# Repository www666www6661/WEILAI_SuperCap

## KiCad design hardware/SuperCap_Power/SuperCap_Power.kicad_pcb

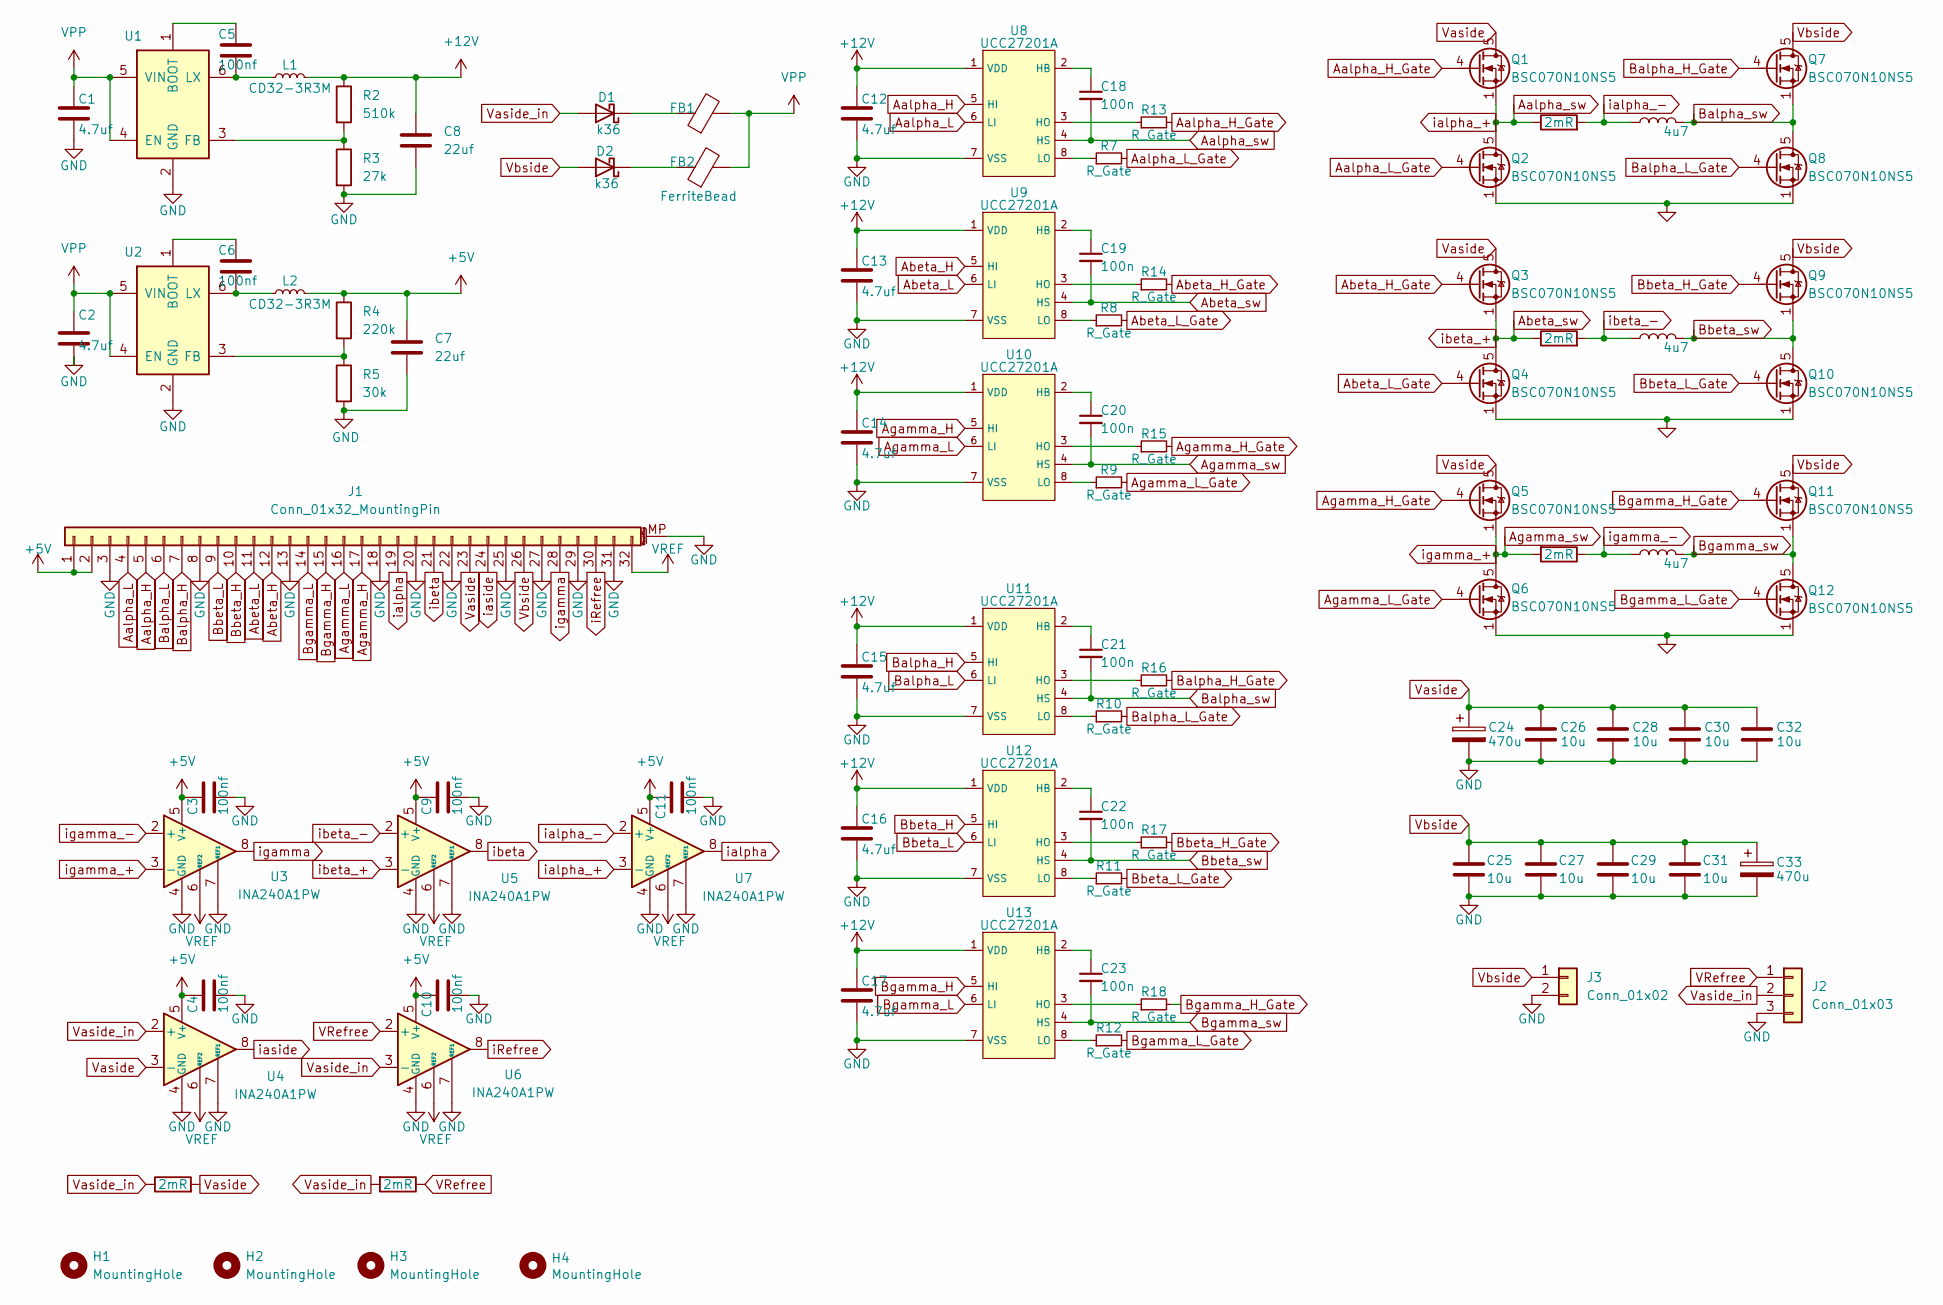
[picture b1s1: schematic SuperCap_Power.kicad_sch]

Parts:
C1, C2: 4.7uf; C_0805_2012Metric
C3, C4, C5, C6, C9, C10, C11: 100nf; C_0603_1608Metric_Pad1.08x0.95mm_HandSolder
C7, C8: 22uf; C_0603_1608Metric_Pad1.08x0.95mm_HandSolder
C12, C13, C14, C15, C16, C17: 4.7uf; C_0603_1608Metric_Pad1.08x0.95mm_HandSolder
C18, C19, C20, C21, C22, C23: 100n; C_0603_1608Metric
C24, C33: 470u; C_Radial_D10.0mm_H20.0mm_P5.00mm
C25, C26, C27, C28, C29, C30, C31, C32: 10u; C_1206_3216Metric
D1, D2: k36; D_SOD-123F
FB1, FB2: FerriteBead; L_0603_1608Metric
H1, H2, H3, H4: MountingHole; MountingHole_3.2mm_M3
J1: Conn_01x32_MountingPin; Hirose_FH12-32S-0.5SH_1x32-1MP_P0.50mm_Horizontal
J2: Conn_01x03; 1_03
J3: Conn_01x02; 01_02
L1, L2: CD32-3R3M; tolerance 20 %; MPN CD32-3R3M
L3, L4, L5: 4u7; L_Bourns_SRP1050WA
Q1, Q2, Q3, Q4, Q5, Q6, Q7, Q8, Q9, Q10, Q11, Q12: BSC070N10NS5; TDSON-8-1
R1, R6, R19, R20, R21: 2mR; R_0612_1632Metric
R2: 510k; R_0603_1608Metric_Pad0.98x0.95mm_HandSolder
R3: 27k; R_0603_1608Metric_Pad0.98x0.95mm_HandSolder
R4: 220k; R_0603_1608Metric_Pad0.98x0.95mm_HandSolder
R5: 30k; R_0603_1608Metric_Pad0.98x0.95mm_HandSolder
R7, R8, R9, R10, R11, R12, R13, R14, R15, R16, R17, R18: R_Gate; R_0603_1608Metric
U1, U2: ME3121AM6G; SOT-23-6; MPN ME3121AM6G
U3, U4, U5, U6, U7: INA240A1PW; TSSOP-8_4.4x3mm_P0.65mm
U8, U9, U10, U11, U12, U13: UCC27201A; SOIC-8_3.9x4.9mm_P1.27mm

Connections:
+5V: C3.2, C4.2, C7.2, C9.2, C10.2, C11.2, J1.1, J1.2, L2.2, R4.1, U3.5 (V+), U4.5 (V+), U5.5 (V+), U6.5 (V+), U7.5 (V+)
+12V: C8.2, C12.1, C13.1, C14.1, C15.1, C16.1, C17.1, L1.2, R2.1, U8.1 (VDD), U9.1 (VDD), U10.1 (VDD), U11.1 (VDD), U12.1 (VDD), U13.1 (VDD)
Aalpha_H: J1.5, U8.5 (HI)
Aalpha_H_Gate: Q1.4 (G), R13.2
Aalpha_L: J1.4, U8.6 (LI)
Aalpha_L_Gate: Q2.4 (G), R7.2
Aalpha_sw: C18.2, Q1.1 (S), Q1.2 (S), Q1.3 (S), Q2.5 (D), R19.1, U7.3 (-), U8.4 (HS)
Abeta_H: J1.12, U9.5 (HI)
Abeta_H_Gate: Q3.4 (G), R14.2
Abeta_L: J1.11, U9.6 (LI)
Abeta_L_Gate: Q4.4 (G), R8.2
Abeta_sw: C19.2, Q3.1 (S), Q3.2 (S), Q3.3 (S), Q4.5 (D), R20.1, U5.3 (-), U9.4 (HS)
Agamma_H: J1.17, U10.5 (HI)
Agamma_H_Gate: Q5.4 (G), R15.2
Agamma_L: J1.16, U10.6 (LI)
Agamma_L_Gate: Q6.4 (G), R9.2
Agamma_sw: C20.2, Q5.1 (S), Q5.2 (S), Q5.3 (S), Q6.5 (D), R21.2, U3.3 (-), U10.4 (HS)
Balpha_H: J1.7, U11.5 (HI)
Balpha_H_Gate: Q7.4 (G), R16.2
Balpha_L: J1.6, U11.6 (LI)
Balpha_L_Gate: Q8.4 (G), R10.2
Balpha_sw: C21.2, L3.2, Q7.1 (S), Q7.2 (S), Q7.3 (S), Q8.5 (D), U11.4 (HS)
Bbeta_H: J1.10, U12.5 (HI)
Bbeta_H_Gate: Q9.4 (G), R17.2
Bbeta_L: J1.9, U12.6 (LI)
Bbeta_L_Gate: Q10.4 (G), R11.2
Bbeta_sw: C22.2, L4.2, Q9.1 (S), Q9.2 (S), Q9.3 (S), Q10.5 (D), U12.4 (HS)
Bgamma_H: J1.15, U13.5 (HI)
Bgamma_H_Gate: Q11.4 (G), R18.2
Bgamma_L: J1.14, U13.6 (LI)
Bgamma_L_Gate: Q12.4 (G), R12.2
Bgamma_sw: C23.2, L5.2, Q11.1 (S), Q11.2 (S), Q11.3 (S), Q12.5 (D), U13.4 (HS)
GND: C1.2, C2.2, C3.1, C4.1, C7.1, C8.1, C9.1, C10.1, C11.1, C12.2, C13.2, C14.2, C15.2, C16.2, C17.2, C24.2, C25.1, C26.1, C27.1, C28.1, C29.1, C30.1, C31.1, C32.1, C33.2, J1.3, J1.8, J1.13, J1.18, J1.20, J1.22, J1.25, J1.27, J1.29, J1.31, J1.MP (MountPin), J2.3, J3.2, Q2.1 (S), Q2.2 (S), Q2.3 (S), Q4.1 (S), Q4.2 (S), Q4.3 (S), Q6.1 (S), Q6.2 (S), Q6.3 (S), Q8.1 (S), Q8.2 (S), Q8.3 (S), Q10.1 (S), Q10.2 (S), Q10.3 (S), Q12.1 (S), Q12.2 (S), Q12.3 (S), R3.2, R5.2, U1.2 (GND), U2.2 (GND), U3.1 (GND), U3.4 (GND), U3.7 (REF1), U4.1 (GND), U4.4 (GND), U4.7 (REF1), U5.1 (GND), U5.4 (GND), U5.7 (REF1), U6.1 (GND), U6.4 (GND), U6.7 (REF1), U7.1 (GND), U7.4 (GND), U7.7 (REF1), U8.7 (VSS), U9.7 (VSS), U10.7 (VSS), U11.7 (VSS), U12.7 (VSS), U13.7 (VSS)
unnamed: D1.1 (K), FB1.1
unnamed: D2.1 (K), FB2.1
unnamed: C5.2, U1.1 (BOOT)
unnamed: R2.2, R3.1, U1.3 (FB)
unnamed: C5.1, L1.1, U1.6 (LX)
unnamed: C6.2, U2.1 (BOOT)
unnamed: R4.2, R5.1, U2.3 (FB)
unnamed: C6.1, L2.1, U2.6 (LX)
unnamed: C18.1, U8.2 (HB)
unnamed: R13.1, U8.3 (HO)
unnamed: R7.1, U8.8 (LO)
unnamed: C19.1, U9.2 (HB)
unnamed: R14.1, U9.3 (HO)
unnamed: R8.1, U9.8 (LO)
unnamed: C20.1, U10.2 (HB)
unnamed: R15.1, U10.3 (HO)
unnamed: R9.1, U10.8 (LO)
unnamed: C21.1, U11.2 (HB)
unnamed: R16.1, U11.3 (HO)
unnamed: R10.1, U11.8 (LO)
unnamed: C22.1, U12.2 (HB)
unnamed: R17.1, U12.3 (HO)
unnamed: R11.1, U12.8 (LO)
unnamed: C23.1, U13.2 (HB)
unnamed: R18.1, U13.3 (HO)
unnamed: R12.1, U13.8 (LO)
VPP: C1.1, C2.1, FB1.2, FB2.2, U1.4 (EN), U1.5 (VIN), U2.4 (EN), U2.5 (VIN)
VREF: J1.32, U3.6 (REF2), U4.6 (REF2), U5.6 (REF2), U6.6 (REF2), U7.6 (REF2)
VRefree: J2.1, R6.1, U6.2 (+)
Vaside: C24.1, C26.2, C28.2, C30.2, C32.2, J1.23, Q1.5 (D), Q3.5 (D), Q5.5 (D), R1.2, U4.3 (-)
Vaside_in: D1.2 (A), J2.2, R1.1, R6.2, U4.2 (+), U6.3 (-)
Vbside: C25.2, C27.2, C29.2, C31.2, C33.1, D2.2 (A), J1.26, J3.1, Q7.5 (D), Q9.5 (D), Q11.5 (D)
iRefree: J1.30, U6.8
ialpha: J1.19, U7.8
ialpha_-: L3.1, R19.2, U7.2 (+)
iaside: J1.24, U4.8
ibeta: J1.21, U5.8
ibeta_-: L4.1, R20.2, U5.2 (+)
igamma: J1.28, U3.8
igamma_-: L5.1, R21.1, U3.2 (+)

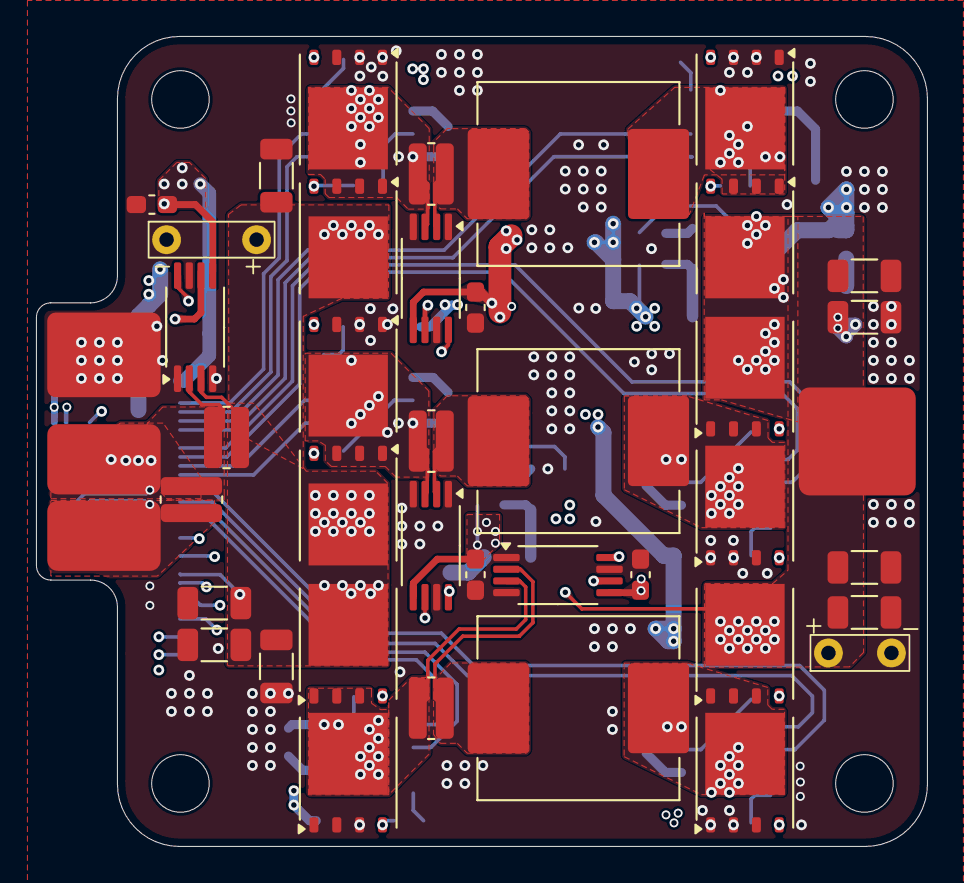
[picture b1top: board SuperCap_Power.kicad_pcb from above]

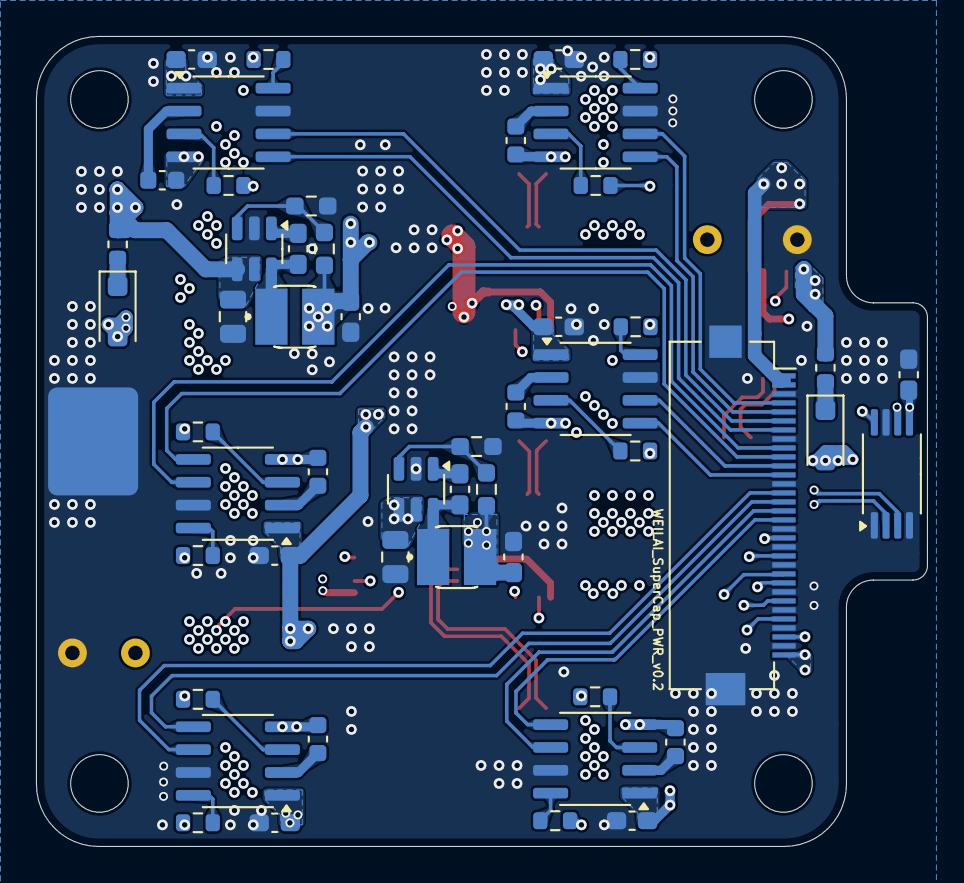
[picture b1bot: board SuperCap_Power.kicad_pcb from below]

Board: 4 copper layers, 49.5 x 45.0 mm, 95 parts (51 on the bottom side), 73 nets.

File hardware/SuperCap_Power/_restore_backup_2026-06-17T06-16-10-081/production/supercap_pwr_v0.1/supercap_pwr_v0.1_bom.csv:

Designator,Footprint,Quantity,Value,LCSC Part #
"C1, C2",0805,2,4.7uf,
"C10, C11, C3, C4, C5, C6, C9",0603,7,100nf,
"C12, C13, C14, C15, C16, C17",0603,6,4.7uf,
"C18, C19, C20, C21, C22, C23",0603,6,100n,
"C24, C33",C_Radial_D10.0mm_H20.0mm_P5.00mm,2,470u,
"C25, C26, C27, C28, C29, C30, C31, C32",1206,8,10u,
"C7, C8",0603,2,22uf,
"D1, D2",D_SOD-123F,2,k36,
"FB1, FB2",0603,2,FerriteBead,
J1,Hirose_FH12-32S-0.5SH_1x32-1MP_P0.50mm_Horizontal,1,Conn_01x32_MountingPin,
J2,1_03,1,Conn_01x03,
J3,01_02,1,Conn_01x02,
"L1, L2",CD32-3R3M,2,CD32-3R3M,CD32-3R3M
"L3, L4, L5",L_Bourns_SRP1050WA,3,4u7,
"Q1, Q10, Q11, Q12, Q2, Q3, Q4, Q5, Q6, Q7, Q8, Q9",TDSON-8-1,12,BSC070N10NS5,
"R1, R19, R20, R21, R6",0612,5,2mR,
"R10, R11, R12, R13, R14, R15, R16, R17, R18, R7, R8, R9",0603,12,R_Gate,
R2,0603,1,510k,
R3,0603,1,27k,
R4,0603,1,220k,
R5,0603,1,30k,
"U1, U2",SOT-23-6,2,ME3121AM6G,ME3121AM6G
"U10, U11, U12, U13, U8, U9",SOIC-8_3.9x4.9mm_P1.27mm,6,UCC27201A,
"U3, U4, U5, U6, U7",TSSOP-8_4.4x3mm_P0.65mm,5,INA240A1PW,

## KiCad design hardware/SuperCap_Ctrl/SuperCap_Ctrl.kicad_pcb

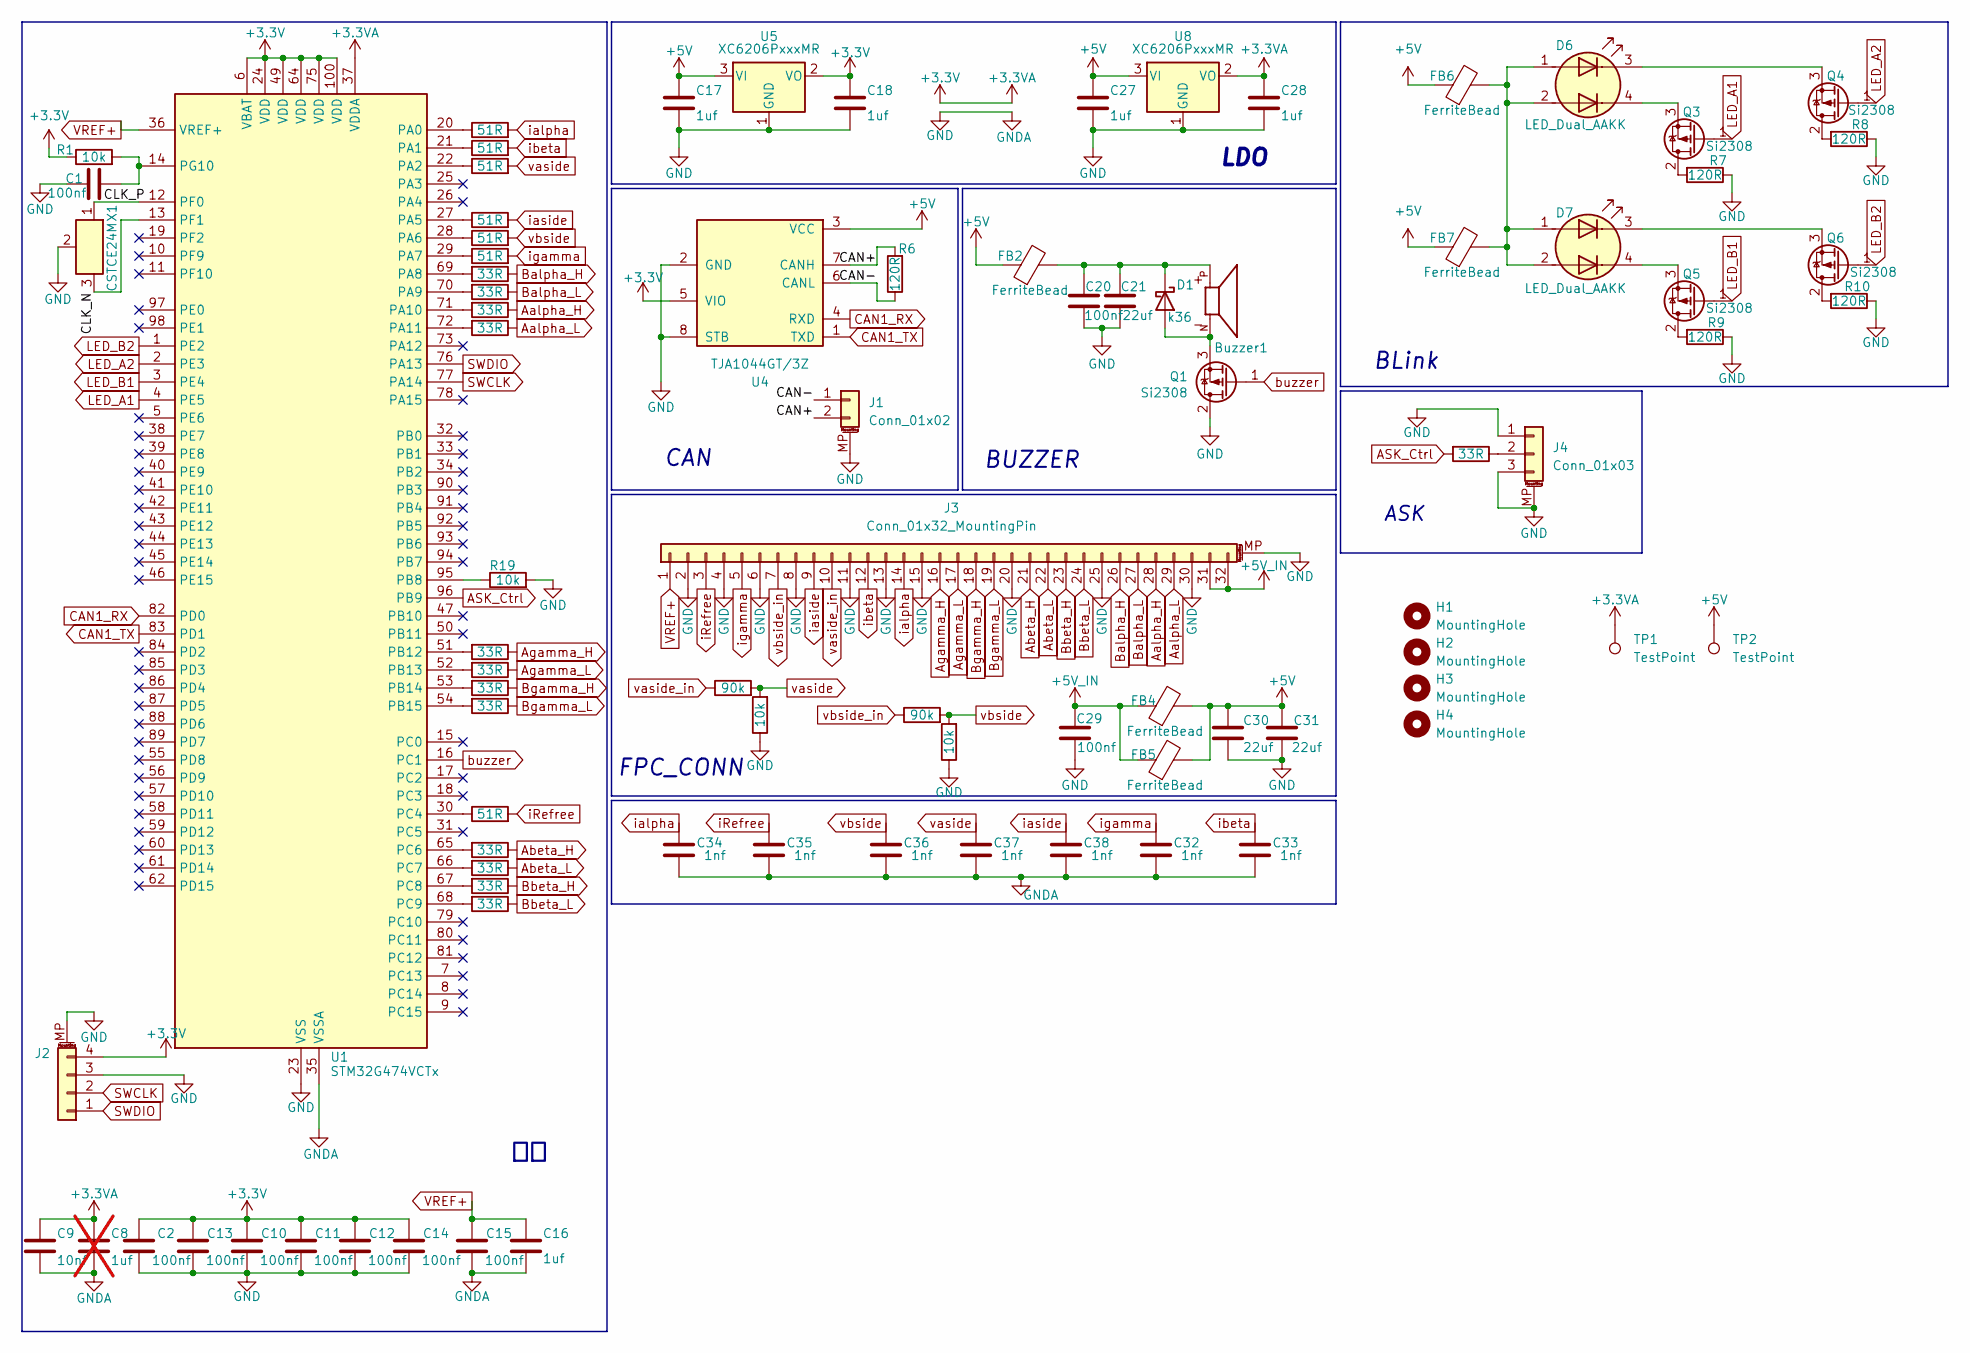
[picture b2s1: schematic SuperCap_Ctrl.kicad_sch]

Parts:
Buzzer1: CMT-7525-80-SMT-TR; XDCR_CMT-7525-80-SMT-TR; PARTREV N/A
C1, C2, C10, C11, C12, C13, C14, C15, C20, C29: 100nf; C_0603_1608Metric_Pad1.08x0.95mm_HandSolder
C8: 1uf; C_0603_1608Metric_Pad1.08x0.95mm_HandSolder; not fitted
C9: 10nf; C_0603_1608Metric_Pad1.08x0.95mm_HandSolder
C16, C17, C18, C27, C28: 1uf; C_0603_1608Metric_Pad1.08x0.95mm_HandSolder
C21, C30, C31: 22uf; C_0603_1608Metric_Pad1.08x0.95mm_HandSolder
C32, C33, C34, C35, C36, C37, C38: 1nf; C_0603_1608Metric_Pad1.08x0.95mm_HandSolder
D1: k36; D_SOD-123F
D6, D7: LED_Dual_AAKK; LED_Avago_PLCC4_3.2x2.8mm_CW
FB2, FB4, FB5, FB6, FB7: FerriteBead; L_0603_1608Metric
H1, H2, H3, H4: MountingHole; MountingHole_3.2mm_M3
J1: Conn_01x02; JST_GH_SM02B-GHS-TB_1x02-1MP_P1.25mm_Horizontal
J2: Conn_01x04; Molex_CLIK-Mate_502386-0470_1x04-1MP_P1.25mm_Horizontal
J3: Conn_01x32_MountingPin; Hirose_FH12-32S-0.5SH_1x32-1MP_P0.50mm_Horizontal
J4: Conn_01x03; JST_GH_SM03B-GHS-TB_1x03-1MP_P1.25mm_Horizontal
Q1, Q3, Q4, Q5, Q6: Si2308; SOT-23
R1, R12, R19: 10k; R_0603_1608Metric
R2, R30, R31, R32, R33, R34, R35, R36, R37, R38, R39, R40, R41: 33R; R_0603_1608Metric_Pad0.98x0.95mm_HandSolder
R3, R11: 90k; R_0603_1608Metric
R4: 10k; R_0603_1608Metric_Pad0.98x0.95mm_HandSolder
R6, R7, R8, R9, R10: 120R; R_0603_1608Metric_Pad0.98x0.95mm_HandSolder
R23, R24, R25, R26, R27, R28, R29: 51R; R_0603_1608Metric_Pad0.98x0.95mm_HandSolder
TP1, TP2: TestPoint; TestPoint_Pad_D1.0mm
U1: STM32G474VCTx; LQFP-100_14x14mm_P0.5mm
U4: TJA1044GT/3Z; SOIC-8_3.9x4.9mm_P1.27mm; MPN TJA1044GT/3Z
U5, U8: XC6206PxxxMR; SOT-23-3
X1: CSTCE24M; OSC_CSTCE8M00G55-R0; tolerance 0.1 %; MPN CSTCE8M00G15C99-R0

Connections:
+3.3V: C2.1, C8.2, C9.2, C10.1, C11.1, C12.1, C13.1, C14.1, C18.2, C28.2, J2.4, R1.1, TP1.1, U1.6 (VBAT), U1.24 (VDD), U1.37 (VDDA), U1.49 (VDD), U1.64 (VDD), U1.75 (VDD), U1.100 (VDD), U4.5 (VIO), U5.2 (VO), U8.2 (VO)
+5V: C17.2, C27.2, C30.2, C31.2, FB2.1, FB4.2, FB5.2, FB6.1, FB7.1, TP2.1, U4.3 (VCC), U5.3 (VI), U8.3 (VI)
+5V_IN: C29.1, FB4.1, FB5.1, J3.31, J3.32
/CAN+: J1.2, R6.2, U4.7 (CANH)
/CAN-: J1.1, R6.1, U4.6 (CANL)
/CLK_N: U1.13 (PF1), X1.3
/CLK_P: U1.12 (PF0), X1.1
ASK_Ctrl: R2.2, U1.96 (PB9)
Aalpha_H: J3.28, R40.1
Aalpha_L: J3.29, R41.1
Abeta_H: J3.21, R30.1
Abeta_L: J3.22, R31.1
Agamma_H: J3.16, R34.1
Agamma_L: J3.17, R35.1
Balpha_H: J3.26, R38.1
Balpha_L: J3.27, R39.1
Bbeta_H: J3.23, R32.1
Bbeta_L: J3.24, R33.1
Bgamma_H: J3.18, R36.1
Bgamma_L: J3.19, R37.1
CAN1_RX: U1.82 (PD0), U4.4 (RXD)
CAN1_TX: U1.83 (PD1), U4.1 (TXD)
GND: C1.2, C2.2, C8.1, C9.1, C10.2, C11.2, C12.2, C13.2, C14.2, C15.2, C16.1, C17.1, C18.1, C20.2, C21.1, C27.1, C28.1, C29.2, C30.1, C31.1, C32.2, C33.2, C34.2, C35.2, C36.2, C37.2, C38.2, J1.MP (MountPin), J2.3, J2.MP (MountPin), J3.2, J3.4, J3.6, J3.8, J3.11, J3.13, J3.15, J3.20, J3.25, J3.30, J3.MP (MountPin), J4.1, J4.3, J4.MP (MountPin), Q1.2 (D), R4.1, R7.1, R8.1, R9.1, R10.1, R12.1, R19.2, U1.23 (VSS), U1.35 (VSSA), U1.48 (VSS), U1.63 (VSS), U1.74 (VSS), U1.99 (VSS), U4.2 (GND), U4.8 (STB), U5.1 (GND), U8.1 (GND), X1.2
LED_A1: Q3.1 (G), U1.4 (PE5)
LED_A2: Q4.1 (G), U1.2 (PE3)
LED_B1: Q5.1 (G), U1.3 (PE4)
LED_B2: Q6.1 (G), U1.1 (PE2)
unnamed: Buzzer1.N, D1.2 (A), Q1.3 (S)
unnamed: Buzzer1.P, C20.1, C21.2, D1.1 (K), FB2.2
unnamed: D6.1 (A1), D6.2 (A2), D7.1 (A1), D7.2 (A2), FB6.2, FB7.2
unnamed: D6.3 (K1), Q4.3 (S)
unnamed: D6.4 (K2), Q3.3 (S)
unnamed: D7.3 (K1), Q6.3 (S)
unnamed: D7.4 (K2), Q5.3 (S)
unnamed: J4.2, R2.1
unnamed: Q3.2 (D), R7.2
unnamed: Q4.2 (D), R8.2
unnamed: Q5.2 (D), R9.2
unnamed: Q6.2 (D), R10.2
unnamed: R23.1, U1.20 (PA0)
unnamed: R24.1, U1.21 (PA1)
unnamed: R25.1, U1.22 (PA2)
unnamed: R29.1, U1.27 (PA5)
unnamed: R27.1, U1.28 (PA6)
unnamed: R28.1, U1.29 (PA7)
unnamed: R38.2, U1.69 (PA8)
unnamed: R39.2, U1.70 (PA9)
unnamed: R40.2, U1.71 (PA10)
unnamed: R41.2, U1.72 (PA11)
unnamed: R19.1, U1.95 (PB8)
unnamed: R34.2, U1.51 (PB12)
unnamed: R35.2, U1.52 (PB13)
unnamed: R36.2, U1.53 (PB14)
unnamed: R37.2, U1.54 (PB15)
unnamed: R26.1, U1.30 (PC4)
unnamed: R30.2, U1.65 (PC6)
unnamed: R31.2, U1.66 (PC7)
unnamed: R32.2, U1.67 (PC8)
unnamed: R33.2, U1.68 (PC9)
unnamed: C1.1, R1.2, U1.14 (PG10)
SWCLK: J2.2, U1.77 (PA14)
SWDIO: J2.1, U1.76 (PA13)
VREF+: C15.1, C16.2, J3.1, U1.36 (VREF+)
buzzer: Q1.1 (G), U1.16 (PC1)
iRefree: C35.1, J3.3, R26.2
ialpha: C34.1, J3.14, R23.2
iaside: C38.1, J3.9, R29.2
ibeta: C33.1, J3.12, R24.2
igamma: C32.1, J3.5, R28.2
vaside: C37.1, R3.2, R4.2, R25.2
vaside_in: J3.10, R3.1
vbside: C36.1, R11.2, R12.2, R27.2
vbside_in: J3.7, R11.1

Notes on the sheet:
BUZZER
LDO
CAN
FPC_CONN
BLink
ASK

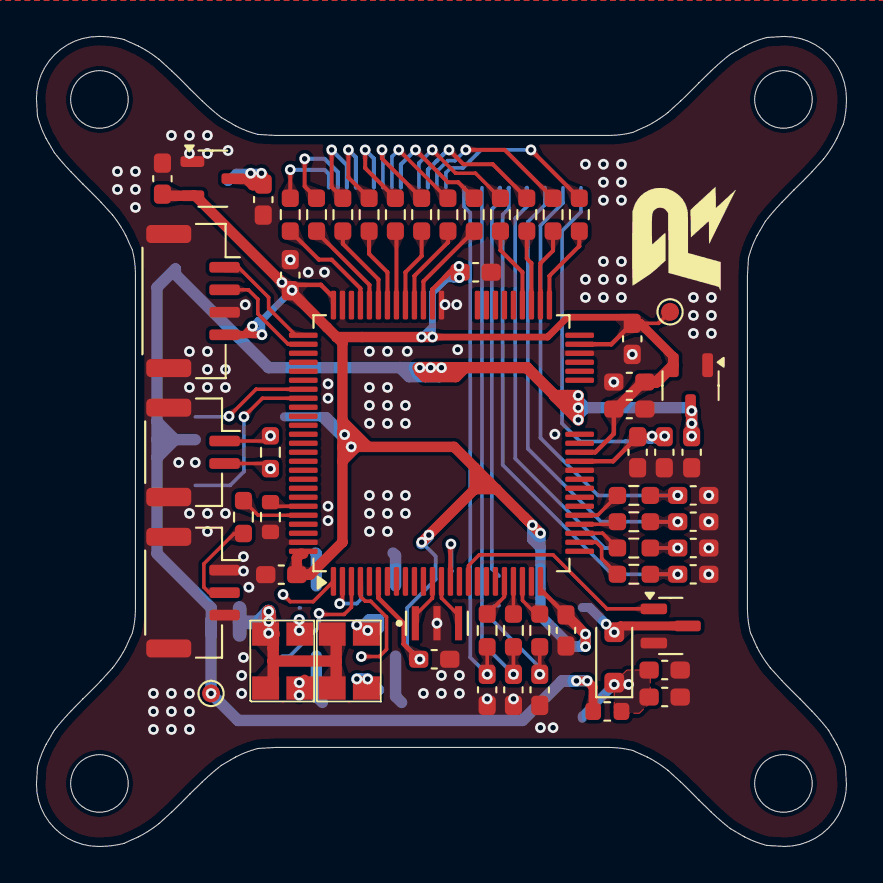
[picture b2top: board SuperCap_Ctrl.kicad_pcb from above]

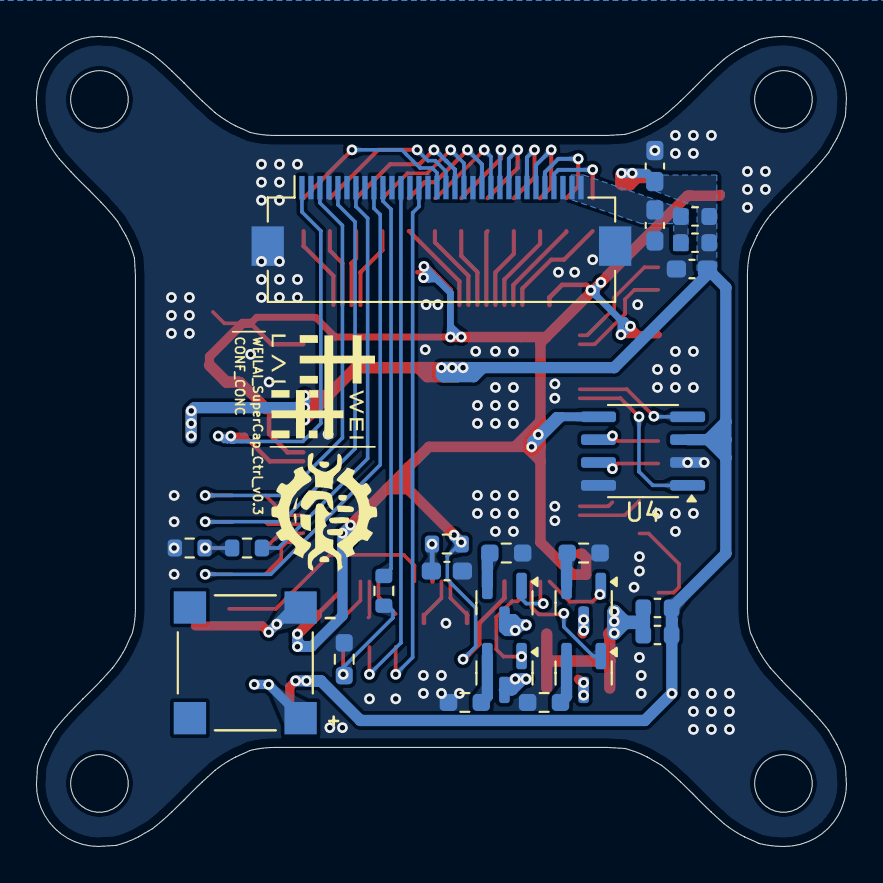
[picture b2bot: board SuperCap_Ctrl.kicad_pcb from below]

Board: 2 copper layers, 45.0 x 45.0 mm, 86 parts (24 on the bottom side), 73 nets.

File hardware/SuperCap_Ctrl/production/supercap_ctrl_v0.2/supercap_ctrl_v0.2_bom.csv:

Designator,Footprint,Quantity,Value,LCSC Part #
BUZZER1,XDCR_CMT-7525-80-SMT-TR,1,CMT-7525-80-SMT-TR,
"C1, C10, C11, C12, C13, C14, C15, C2, C20, C29",0603,10,100nf,
"C16, C17, C18, C27, C28",0603,5,1uf,
"C21, C30, C31",0603,3,22uf,
"C32, C33, C34, C35, C36, C37, C38",0603,7,1nf,
C9,0603,1,10nf,
D1,D_SOD-123F,1,k36,
"D6, D7",LED_Avago_PLCC4_3.2x2.8mm_CW,2,LED_Dual_AAKK,
"FB2, FB4, FB5, FB6, FB7",0603,5,FerriteBead,
J1,JST_GH_SM02B-GHS-TB_1x02-1MP_P1.25mm_Horizontal,1,Conn_01x02,
J2,Molex_CLIK-Mate_502386-0470_1x04-1MP_P1.25mm_Horizontal,1,Conn_01x04,
J3,Hirose_FH12-32S-0.5SH_1x32-1MP_P0.50mm_Horizontal,1,Conn_01x32_MountingPin,
J4,JST_GH_SM03B-GHS-TB_1x03-1MP_P1.25mm_Horizontal,1,Conn_01x03,
"Q1, Q3, Q4, Q5, Q6",SOT-23,5,Si2308,
"R1, R12, R19, R4",0603,4,10k,
"R10, R6, R7, R8, R9",0603,5,120R,
"R11, R3",0603,2,90k,
"R2, R26, R30, R31, R32, R33, R34, R35, R36, R37, R38, R39, R40, R41",0603,14,33R,
"R23, R24, R25, R27, R28, R29",0603,6,51R,
"TP1, TP2",TestPoint_Pad_D1.0mm,2,TestPoint,
U1,LQFP-100_14x14mm_P0.5mm,1,STM32G474VCTx,
U4,SOIC-8_3.9x4.9mm_P1.27mm,1,TJA1044GT/3Z,TJA1044GT/3Z
"U5, U8",SOT-23-3,2,XC6206PxxxMR,
X1,OSC_CSTCE8M00G55-R0,1,CSTCE24M,CSTCE8M00G15C99-R0

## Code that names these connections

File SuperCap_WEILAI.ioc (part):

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Mcu.Name=STM32G474V(B-C-E)Tx
Mcu.Package=LQFP100
Mcu.UserName=STM32G474VCTx
PA0.Mode=IN1-Single-Ended
PA0.Signal=ADC1_IN1
PA1.Mode=IN2-Single-Ended
PA1.Signal=ADC1_IN2
PA10.Mode=Output_TB1TB2
PA10.Signal=HRTIM1_CHB1
PA11.Mode=Output_TB1TB2
PA11.Signal=HRTIM1_CHB2
PA13.Mode=Serial_Wire
PA13.Signal=SYS_JTMS-SWDIO
PA14.Mode=Serial_Wire
PA14.Signal=SYS_JTCK-SWCLK
PA2.Mode=IN3-Single-Ended
PA2.Signal=ADC1_IN3
PA5.Mode=IN13-Single-Ended
PA5.Signal=ADC2_IN13
PA6.Mode=IN3-Single-Ended
PA6.Signal=ADC2_IN3
PA7.Mode=IN4-Single-Ended
PA7.Signal=ADC2_IN4
PA8.Mode=Output_TA1TA2
PA8.Signal=HRTIM1_CHA1
PA9.Mode=Output_TA1TA2
PA9.Signal=HRTIM1_CHA2
PB12.Mode=Output_TC1TC2
PB12.Signal=HRTIM1_CHC1
PB13.Mode=Output_TC1TC2
PB13.Signal=HRTIM1_CHC2
PB14.Mode=Output_TD1TD2
PB14.Signal=HRTIM1_CHD1
PB15.Mode=Output_TD1TD2
PB15.Signal=HRTIM1_CHD2
PB3.Mode=Asynchronous
PB3.Signal=USART2_TX
PB4.Mode=Asynchronous
PB4.Signal=USART2_RX
PB9.Mode=PWM Generation3 CH3N
PB9.Signal=TIM1_CH3N
PC1.GPIOParameters=GPIO_PuPd
PC1.GPIO_PuPd=GPIO_PULLDOWN
PC1.Signal=S_TIM1_CH2
PC2.Mode=IN8-Single-Ended
PC2.Signal=ADC1_IN8
PC4.Mode=IN5-Single-Ended
PC4.Signal=ADC2_IN5
PC6.Mode=Output_TF1TF2
PC6.Signal=HRTIM1_CHF1
PC7.Mode=Output_TF1TF2
PC7.Signal=HRTIM1_CHF2
PC8.Mode=Output_TE1TE2
PC8.Signal=HRTIM1_CHE1
PC9.Mode=Output_TE1TE2
PC9.Signal=HRTIM1_CHE2
PD0.Mode=FDCAN_Activate
PD0.Signal=FDCAN1_RX
PD1.Mode=FDCAN_Activate
PD1.Signal=FDCAN1_TX
PE2.GPIOParameters=PinState,GPIO_PuPd,GPIO_ModeDefaultOutputPP
PE2.GPIO_ModeDefaultOutputPP=GPIO_MODE_OUTPUT_PP
PE2.GPIO_PuPd=GPIO_PULLDOWN
PE2.PinState=GPIO_PIN_RESET
PE2.Signal=GPIO_Output
PE3.GPIOParameters=PinState,GPIO_PuPd,GPIO_ModeDefaultOutputPP
PE3.GPIO_ModeDefaultOutputPP=GPIO_MODE_OUTPUT_PP
PE3.GPIO_PuPd=GPIO_PULLDOWN
PE3.PinState=GPIO_PIN_RESET
PE3.Signal=GPIO_Output
PE4.GPIOParameters=PinState,GPIO_PuPd
PE4.GPIO_PuPd=GPIO_PULLDOWN
PE4.PinState=GPIO_PIN_RESET
PE4.Signal=GPIO_Output
PE5.GPIOParameters=PinState,GPIO_PuPd
PE5.GPIO_PuPd=GPIO_PULLDOWN
PE5.PinState=GPIO_PIN_RESET
PE5.Signal=GPIO_Output
PF0-OSC_IN.Mode=HSE-External-Oscillator
PF0-OSC_IN.Signal=RCC_OSC_IN
PF1-OSC_OUT.Mode=HSE-External-Oscillator
PF1-OSC_OUT.Signal=RCC_OSC_OUT
RCC.HSE_VALUE=20000000
RCC.SYSCLKFreq_VALUE=170000000
RCC.SYSCLKSource=RCC_SYSCLKSOURCE_PLLCLK
board=custom

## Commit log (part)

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2026-03-03 超电上板 v0.1
2026-03-03 init mainrepo
2026-03-03 超电下板 v0.1
2026-03-03 supercap_ctrl_v0.1
2026-03-28 将3D模型保存到项目目录,修复了mos的问题
2026-03-28 wip: before subtree sync
2026-03-28 更新上板,将上板的3D模型存入项目文件夹
2026-03-28 修改LED电路
2026-03-28 修改LED电路_1
